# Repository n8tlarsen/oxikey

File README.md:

# Oxikey
The Rust infused, ultra-clean firmware library for building custom keyboards and other HID USB devices.

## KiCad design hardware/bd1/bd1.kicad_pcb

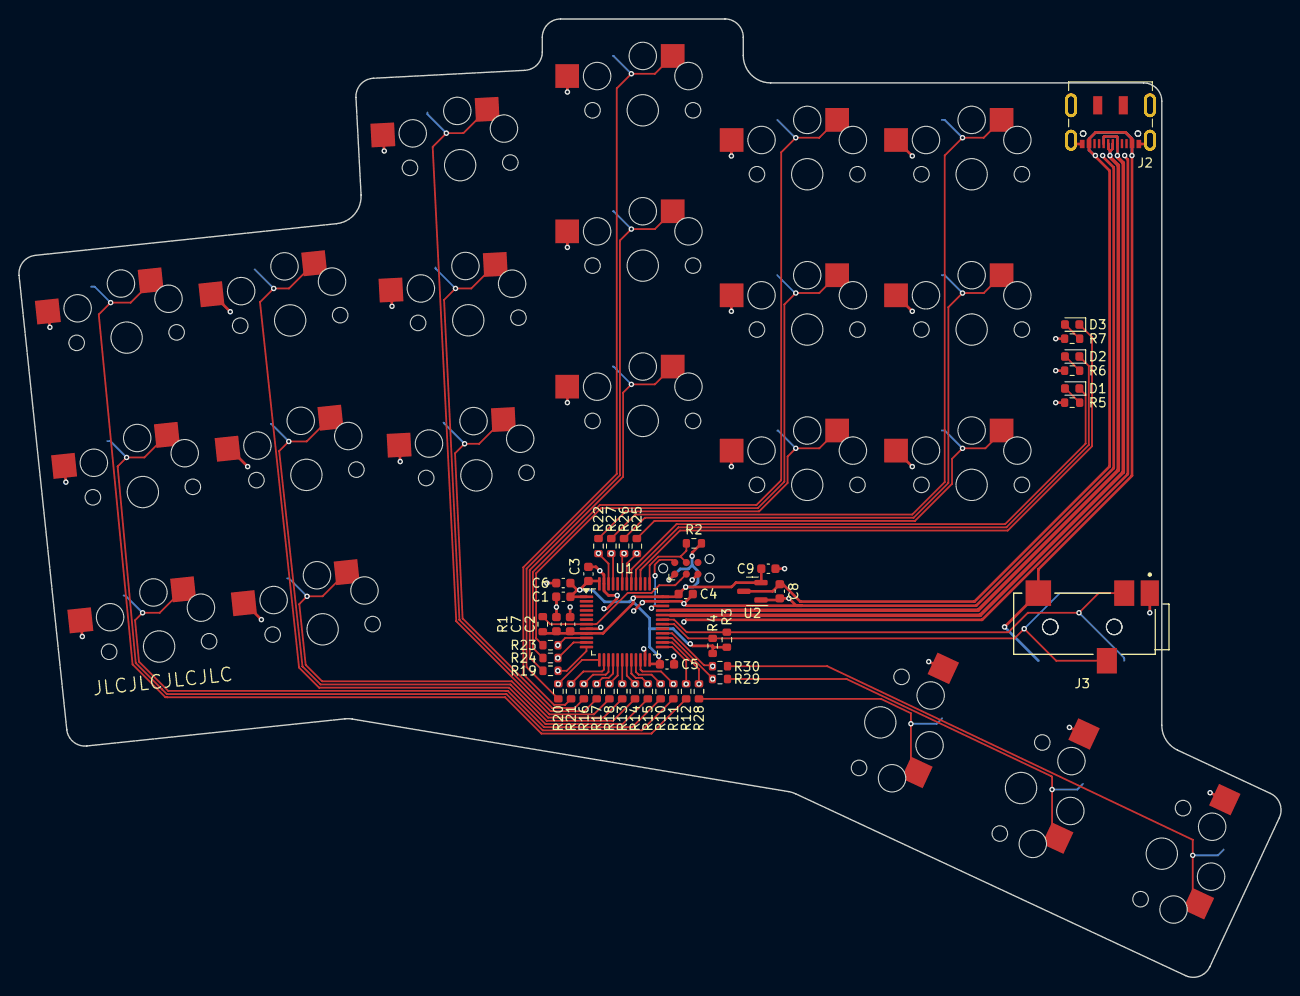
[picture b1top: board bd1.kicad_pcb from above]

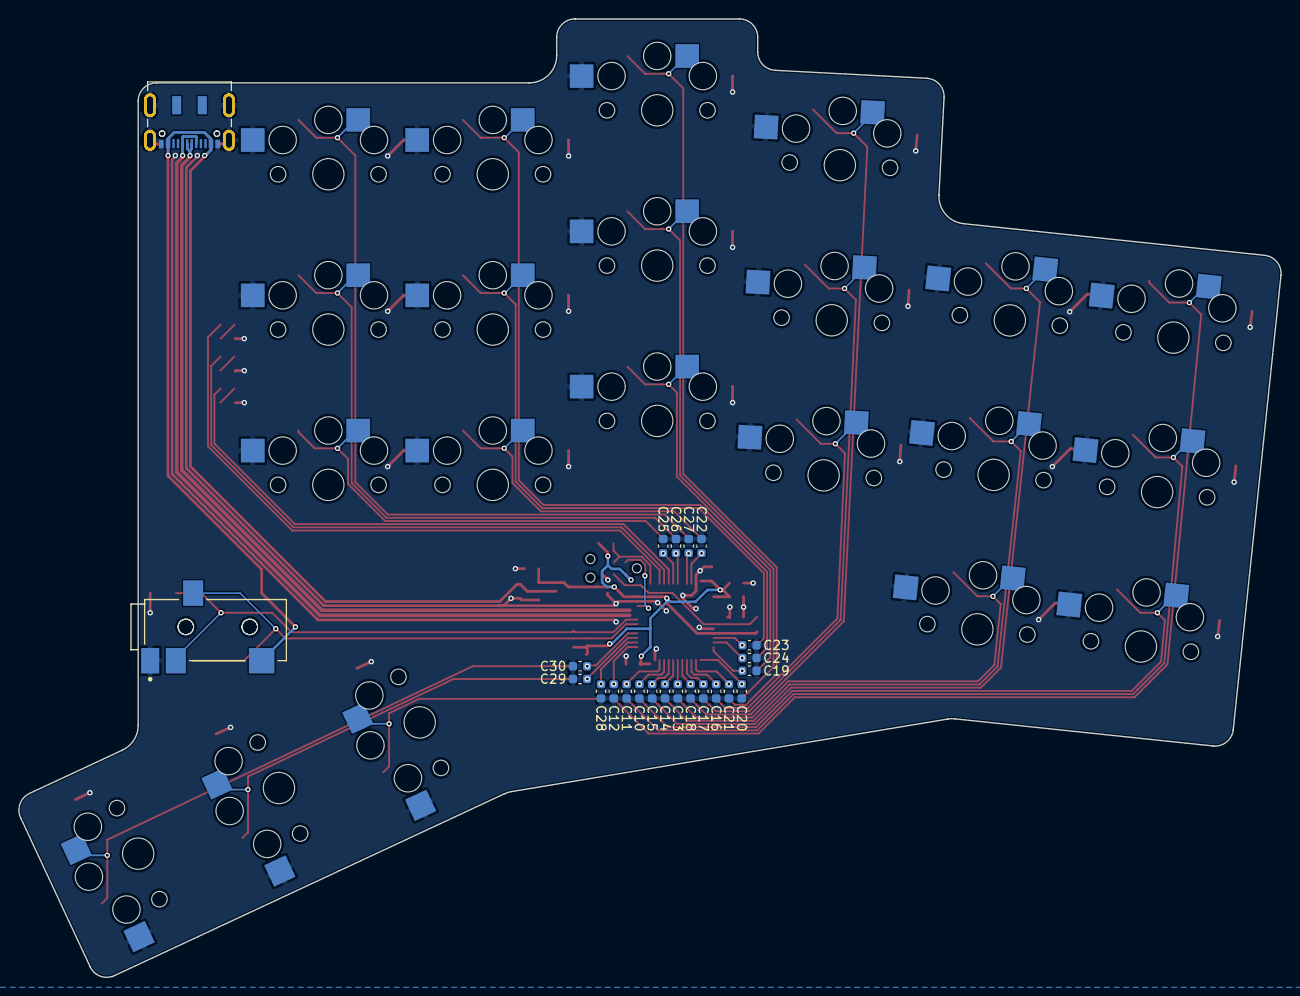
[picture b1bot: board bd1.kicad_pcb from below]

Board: 2 copper layers, 138.2 x 104.9 mm, 89 parts (23 on the bottom side), 58 nets.

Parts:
C1, C2, C3, C4, C5: 0.1uF; C_0603_1608Metric
C6: 4.7uF; C_0603_1608Metric
C7, C8, C9: 1uF; C_0603_1608Metric
C10, C11, C12, C13, C14, C15, C16, C17, C18, C19, C20, C21, C22, C23, C24, C25, C26, C27, C28, C29, C30: 4700p; C_0603_1608Metric
D1, D2, D3: LED; D_0603_1608Metric
J1: Conn_02x03_Odd_Even; Tag-Connect_TC2030-IDC-NL_2x03_P1.27mm_Vertical
J2, J20: USB_C_Receptacle_USB2.0; USB_C_Receptacle_JAE_DX07S016JA1R1500
J3, J30: SJ-43514; CUI-SJ-43514-SMT-0
R1, R3, R4: 10k; R_0603_1608Metric
R2: 1k; R_0603_1608Metric
R5, R6, R7, R10, R11, R12, R13, R14, R15, R16, R17, R18, R19, R20, R21, R22, R23, R24, R25, R26, R27, R28, R29, R30: 470; R_0603_1608Metric
S1, S2, S3, S4, S5, S6, S7, S8, S9, S10, S11, S12, S13, S14, S15, S16, S17, S18, S19, S20, S21: PG1350
U1: STM32L412CBTx; LQFP-48_7x7mm_P0.5mm
U2: AP2127N-3.3; SOT-23

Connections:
+3V3: C1.1, C2.1, C3.1, C4.1, C5.1, C6.1, C7.1, C9.1, J1.1, R1.1, R2.1, R3.1, R4.1, U1.1 (VBAT), U1.9 (VDDA), U1.24 (VDD), U1.36 (VDDUSB), U1.48 (VDD), U2.2 (VO)
+5V: C8.1, J2.A4 (VBUS), J2.A9 (VBUS), J2.B4 (VBUS), J2.B9 (VBUS), J3.2 (Tip), J20.A4 (VBUS), J20.A9 (VBUS), J20.B4 (VBUS), J20.B9 (VBUS), J30.2 (Tip), U2.3 (VI)
/LED0: D1.1 (K), U1.41 (PB5)
/LED1: D2.1 (K), U1.40 (PB4)
/LED2: D3.1 (K), U1.39 (PB3)
/PA00: C23.1, R23.2, U1.10 (PA0)
/PA01: C24.1, R24.2, U1.11 (PA1)
/PA02: C19.1, R19.2, U1.12 (PA2)
/PA03: C20.1, R20.2, U1.13 (PA3)
/PA04: C21.1, R21.2, U1.14 (PA4)
/PA05: C16.1, R16.2, U1.15 (PA5)
/PA06: C17.1, R17.2, U1.16 (PA6)
/PA07: C18.1, R18.2, U1.17 (PA7)
/PB00: C13.1, R13.2, U1.18 (PB0)
/PB01: C14.1, R14.2, U1.19 (PB1)
/PB02: C15.1, R15.2, U1.20 (PB2)
/PB06: C25.1, R25.2, U1.42 (PB6)
/PB07: C26.1, R26.2, U1.43 (PB7)
/PB08: C27.1, R27.2, U1.45 (PB8)
/PB09: C22.1, R22.2, U1.46 (PB9)
/PB10: C10.1, R10.2, U1.21 (PB10)
/PB11: C11.1, R11.2, U1.22 (PB11)
/PB12: C12.1, R12.2, U1.25 (PB12)
/PB13: C28.1, R28.2, U1.26 (PB13)
/PB14: C29.1, R29.2, U1.27 (PB14)
/PB15: C30.1, R30.2, U1.28 (PB15)
/RESETn: J1.3, R1.2, U1.7 (NRST)
/SCL: J3.3 (Ring1), J30.3 (Ring1), R4.2, U1.30 (PA9)
/SDA: J3.4 (Ring2), J30.4 (Ring2), R3.2, U1.31 (PA10)
/SWCLK: J1.4, R2.2, U1.37 (PA14)
/SWDIO: J1.2, U1.34 (PA13)
/USB_DN: J2.A7 (D-), J2.B7 (D-), J20.A7 (D-), J20.B7 (D-), U1.32 (PA11)
/USB_DP: J2.A6 (D+), J2.B6 (D+), J20.A6 (D+), J20.B6 (D+), U1.33 (PA12)
/far_thumb: R30.1, S21.1
/home_thumb: R29.1, S20.1
/index_bottom: R22.1, S13.1
/index_home: R23.1, S14.1
/index_top: R24.1, S15.1
/inner_bottom: R25.1, S16.1
/inner_home: R26.1, S17.1
/inner_top: R27.1, S18.1
/middle_bottom: R19.1, S10.1
/middle_home: R20.1, S11.1
/middle_top: R21.1, S12.1
/near_thumb: R28.1, S19.1
/outer_bottom: R10.1, S1.1
/outer_home: R11.1, S2.1
/outer_top: R12.1, S3.1
/pinky_bottom: R13.1, S4.1
/pinky_home: R14.1, S5.1
/pinky_top: R15.1, S6.1
/ring_bottom: R16.1, S7.1
/ring_home: R17.1, S8.1
/ring_top: R18.1, S9.1
GND: C1.2, C2.2, C3.2, C4.2, C5.2, C6.2, C7.2, C8.2, C9.2, C10.2, C11.2, C12.2, C13.2, C14.2, C15.2, C16.2, C17.2, C18.2, C19.2, C20.2, C21.2, C22.2, C23.2, C24.2, C25.2, C26.2, C27.2, C28.2, C29.2, C30.2, J1.5, J2.A1 (GND), J2.A12 (GND), J2.B1 (GND), J2.B12 (GND), J2.S1 (SHIELD), J3.1 (Sleeve), J20.A1 (GND), J20.A12 (GND), J20.B1 (GND), J20.B12 (GND), J20.S1 (SHIELD), J30.1 (Sleeve), R5.2, R6.2, R7.2, S1.2, S2.2, S3.2, S4.2, S5.2, S6.2, S7.2, S8.2, S9.2, S10.2, S11.2, S12.2, S13.2, S14.2, S15.2, S16.2, S17.2, S18.2, S19.2, S20.2, S21.2, U1.8 (VSSA), U1.23 (VSS), U1.35 (VSS), U1.47 (VSS), U2.1 (GND)
unnamed: D1.2 (A), R5.1
unnamed: D2.2 (A), R6.1
unnamed: D3.2 (A), R7.1

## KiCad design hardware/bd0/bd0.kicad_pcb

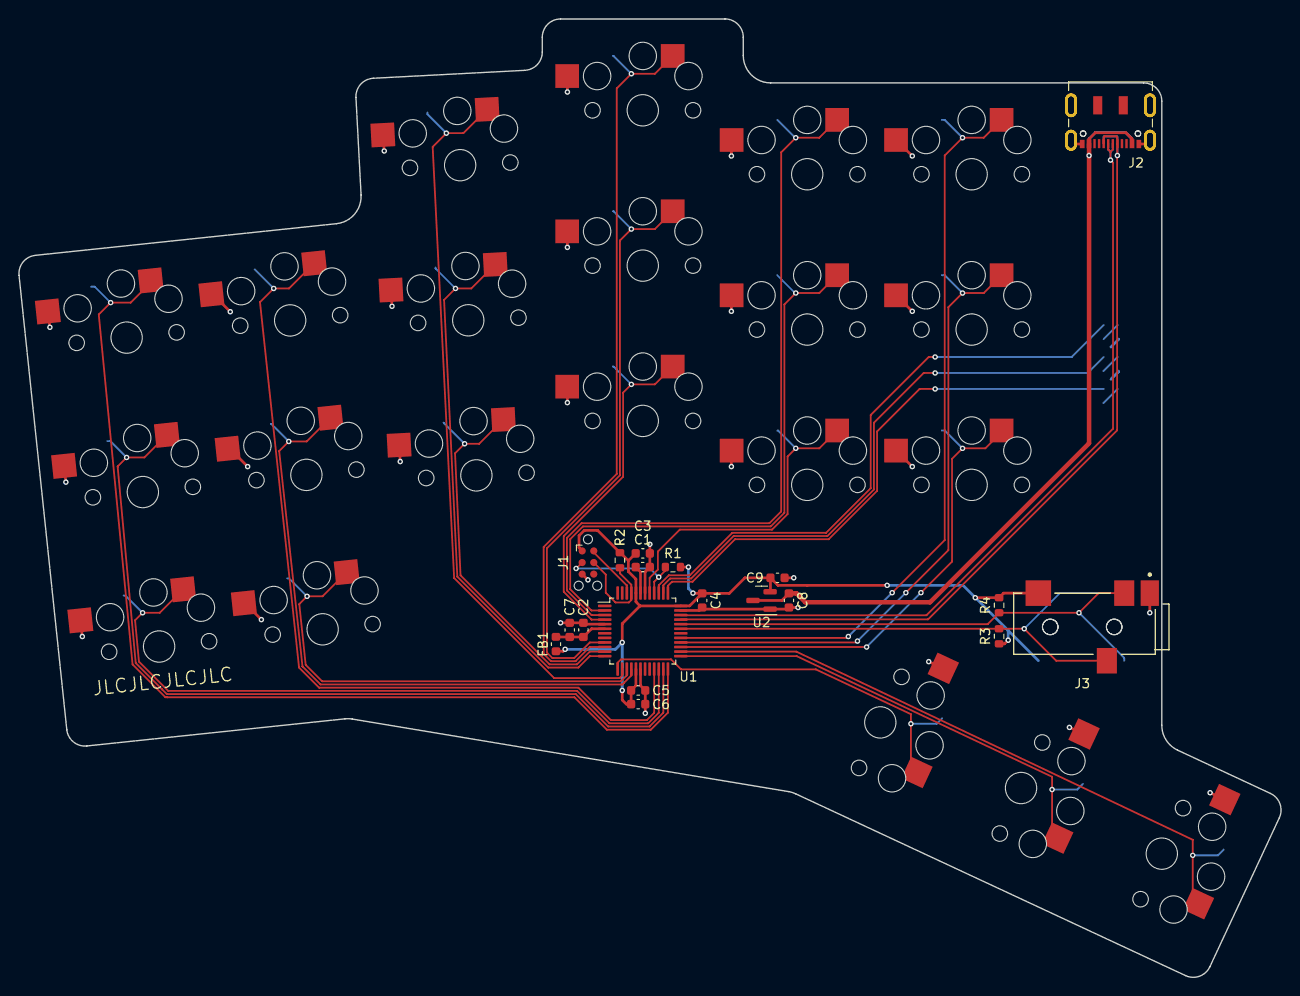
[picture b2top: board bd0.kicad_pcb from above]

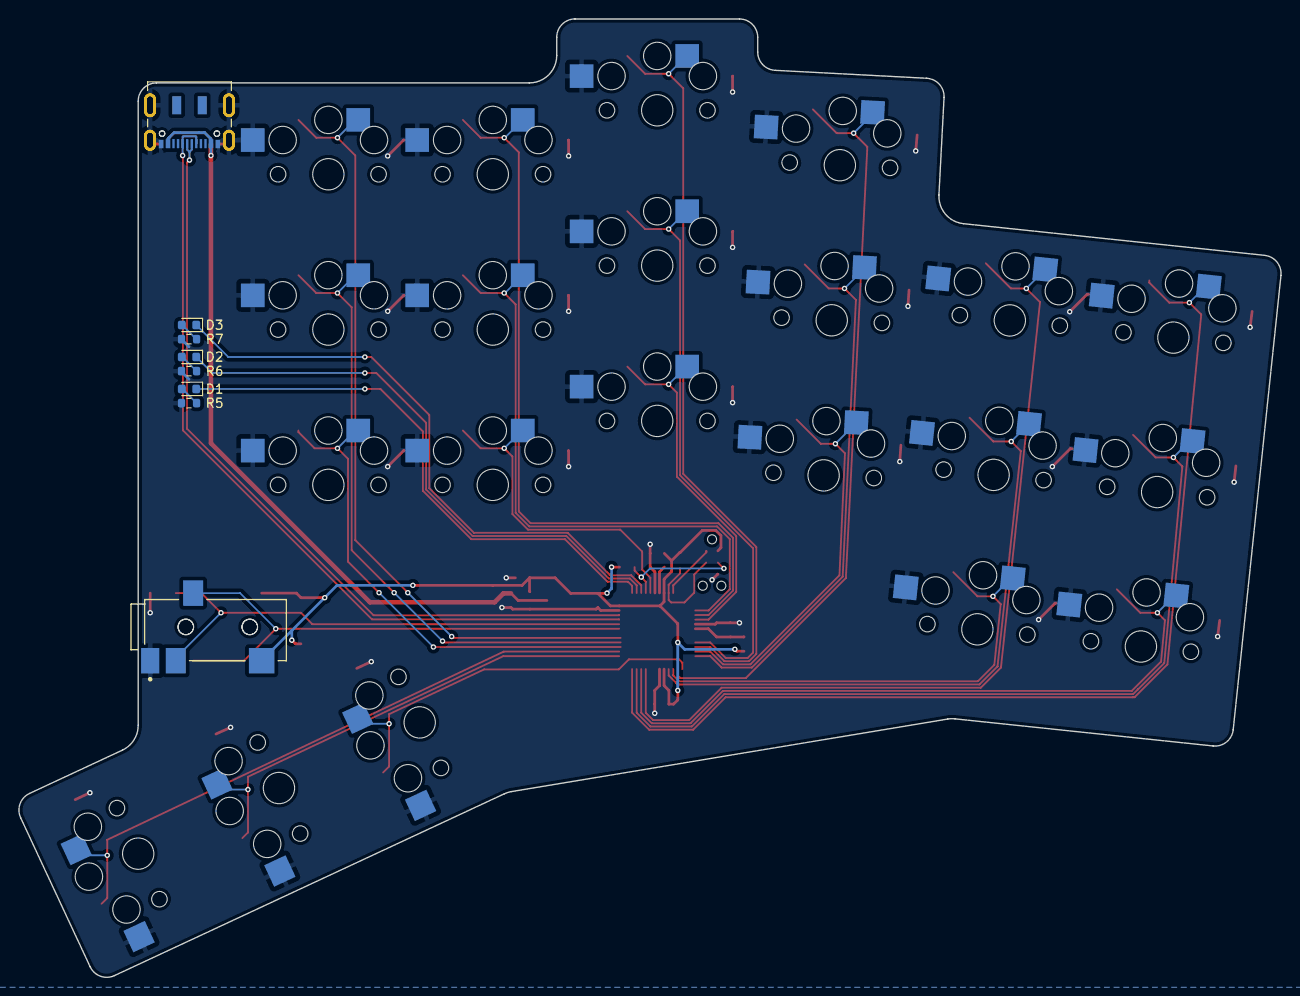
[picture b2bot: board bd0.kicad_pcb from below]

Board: 2 copper layers, 138.2 x 104.9 mm, 48 parts (8 on the bottom side), 39 nets.

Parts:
C1, C8, C9: 1uF; C_0603_1608Metric
C2, C3, C4, C5: 0.1uF; C_0603_1608Metric
C6, C7: 10uF; C_0603_1608Metric
D1, D2, D3: LED; D_0603_1608Metric
FB1: FerriteBead; L_0603_1608Metric
J1: Conn_02x03_Odd_Even; Tag-Connect_TC2030-IDC-NL_2x03_P1.27mm_Vertical
J2, J20: USB_C_Receptacle_USB2.0; USB_C_Receptacle_JAE_DX07S016JA1R1500
J3, J30: SJ-43514; CUI-SJ-43514-SMT-0
R1, R3, R4: 10k; R_0603_1608Metric
R2: 1k; R_0603_1608Metric
R5, R6, R7: 470; R_0603_1608Metric
S1, S2, S3, S4, S5, S6, S7, S8, S9, S10, S11, S12, S13, S14, S15, S16, S17, S18, S19, S20, S21: PG1350
U1: ATSAMD21G15B-A; TQFP-48_7x7mm_P0.5mm
U2: AP2127N-3.3; SOT-23

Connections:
+1V2: C1.1, U1.43 (VDDCORE)
+3V3: C3.1, C4.1, C5.1, C6.1, C9.1, FB1.1, J1.1, J3.2 (Tip), J30.2 (Tip), R1.1, R2.1, R3.1, R4.1, U1.17 (VDDIO), U1.36 (VDDIO), U1.44 (VDDIN), U2.2 (VO)
+5V: C8.1, J2.A4 (VBUS), J2.A9 (VBUS), J2.B4 (VBUS), J2.B9 (VBUS), J20.A4 (VBUS), J20.A9 (VBUS), J20.B4 (VBUS), J20.B9 (VBUS), U2.3 (VI)
/3V3A: C2.1, C7.1, FB1.2, U1.6 (VDDANA)
/LED0: D1.1 (K), U1.37 (PB22)
/LED1: D2.1 (K), U1.38 (PB23)
/LED2: D3.1 (K), U1.39 (PA27)
/RESETn: J1.3, R1.2, U1.40 (~RESET)
/SCL: J3.4 (Ring2), J30.4 (Ring2), R4.2, U1.32 (PA23)
/SDA: J3.3 (Ring1), J30.3 (Ring1), R3.2, U1.31 (PA22)
/SWCLK: J1.4, R2.2, U1.45 (PA30)
/SWDIO: J1.2, U1.46 (PA31)
/USB_DN: J2.A7 (D-), J2.B7 (D-), J20.A7 (D-), J20.B7 (D-), U1.33 (PA24)
/USB_DP: J2.A6 (D+), J2.B6 (D+), J20.A6 (D+), J20.B6 (D+), U1.34 (PA25)
/far_thumb: S21.1, U1.26 (PA17)
/home_thumb: S20.1, U1.25 (PA16)
/index_bottom: S13.1, U1.41 (PA28)
/index_home: S14.1, U1.2 (PA01)
/index_top: S15.1, U1.3 (PA02)
/inner_bottom: S16.1, U1.27 (PA18)
/inner_home: S17.1, U1.28 (PA19)
/inner_top: S18.1, U1.29 (PA20)
/middle_bottom: S10.1, U1.4 (PA03)
/middle_home: S11.1, U1.9 (PA04)
/middle_top: S12.1, U1.10 (PA05)
/near_thumb: S19.1, U1.13 (PA08)
/outer_bottom: S1.1, U1.22 (PA13)
/outer_home: S2.1, U1.23 (PA14)
/outer_top: S3.1, U1.24 (PA15)
/pinky_bottom: S4.1, U1.15 (PA10)
/pinky_home: S5.1, U1.16 (PA11)
/pinky_top: S6.1, U1.21 (PA12)
/ring_bottom: S7.1, U1.11 (PA06)
/ring_home: S8.1, U1.12 (PA07)
/ring_top: S9.1, U1.14 (PA09)
GND: C1.2, C2.2, C3.2, C4.2, C5.2, C6.2, C7.2, C8.2, C9.2, J1.5, J2.A1 (GND), J2.A12 (GND), J2.B1 (GND), J2.B12 (GND), J2.S1 (SHIELD), J3.1 (Sleeve), J20.A1 (GND), J20.A12 (GND), J20.B1 (GND), J20.B12 (GND), J20.S1 (SHIELD), J30.1 (Sleeve), R5.2, R6.2, R7.2, S1.2, S2.2, S3.2, S4.2, S5.2, S6.2, S7.2, S8.2, S9.2, S10.2, S11.2, S12.2, S13.2, S14.2, S15.2, S16.2, S17.2, S18.2, S19.2, S20.2, S21.2, U1.5 (GNDANA), U1.18 (GND), U1.35 (GND), U1.42 (GND), U2.1 (GND)
unnamed: D1.2 (A), R5.1
unnamed: D2.2 (A), R6.1
unnamed: D3.2 (A), R7.1

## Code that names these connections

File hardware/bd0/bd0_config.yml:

points:
  key:
    padding: cy
    footprints:
      keychoc:
        type: choc
        nets:
          from: =keynet
          to: GND
        params:
          hotswap: true
          reverse: true
          keycaps: true
  zones:
    matrix:
      anchor:
      rows:
        bottom:
          bind: [1,2,1,2]
        home:
          bind: [1,2,1,2]
        top:
          bind: [1,2,1,2]
      columns:
        outer:
          spread: cx
          rotate: 6
          row_overrides:
            bottom:
              keynet: /outer_bottom
            home:
              keynet: /outer_home
            top:
              keynet: /outer_top
        pinky:
          spread: cx
          row_overrides:
            bottom:
              keynet: /pinky_bottom
            home:
              keynet: /pinky_home
            top:
              keynet: /pinky_top
        ring:
          spread: cx+0.5
          rotate: -3
          stagger: 15
          row_overrides:
            bottom:
              keynet: /ring_bottom
            home:
              keynet: /ring_home
            top:
              keynet: /ring_top
        middle:
          spread: cx+0.5
          rotate: -3
          stagger: 5
          row_overrides:
            bottom:
              keynet: /middle_bottom
            home:
              keynet: /middle_home
            top:
              keynet: /middle_top
        index:
          spread: cx
          stagger: -7
          row_overrides:
            bottom:
              keynet: /index_bottom
            home:
              keynet: /index_home
            top:
              keynet: /index_top
        inner:
          spread: cx
          row_overrides:
            bottom:
              keynet: /inner_bottom
            home:
              keynet: /inner_home
            top:
              keynet: /inner_top
    thumbfan:
      anchor:
        ref: matrix_inner_bottom
        shift: [-10, -26]
        rotate: -25
      rows:
        thumb:
          bind: [1,2,1,2]
      columns:
        near:
          key:
            rotate: -90
          row_overrides:
            thumb:
              keynet: /near_thumb
        home:
          spread: cy
          key:
            rotate: -90
          row_overrides:
            thumb:
              keynet: /home_thumb
        far:
          spread: cy
          key:
            rotate: -90
          row_overrides:
            thumb:
              keynet: /far_thumb
outlines:
  exports:
    raw:
      - type: keys
        side: left
        size: [cx, cx]
      - operation: add
        type: polygon
        points: 
          - ref: matrix_pinky_bottom
            shift: [0,-cy/2-1]
          - ref: thumbfan_far_thumb
            # shift: [0   , cy/2]
          - ref: matrix_inner_top
            shift: [20.81446479999999, 1.5+cy/2]
          - ref: matrix_index_top
            shift: [0, 1.5+cy/2]
          # - ref: matrix_inner_bottom
          #   shift: [cx/2,cy/2+1]
          - ref: matrix_index_bottom
          - ref: matrix_pinky_home
    cutout:
      - type: outline
        name: raw
        fillet: 3
      - operation: add
        type: outline
        name: raw
        fillet: 2
    keycap_outlines:
      - type: keys
        side: left
        size: [cx-0.5, cy-0.5]
        bound: false

pcbs:
  bd0:
    outlines:
      bd:
        outline: cutout

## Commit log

2022-08-07 Add base files from rust-embedded/cortex-m-quickstart
2022-08-13 Add basic RTIC framework
2022-08-14 Add module for device initialization
2022-08-19 Condense setup to a single function
2022-08-28 Fix crashing issue when starting DFLL
2022-09-01 Use semihosting only in debug configuration
2022-09-05 Use forked HAL for clock setup
2022-09-24 Clock at 48MHz with 1Hz blink
2022-09-25 Add usbd-hid
2022-11-29 USB HID device connected to PC
2022-11-30 Migrate setup from dev board to real keyboard
2022-11-30 Restructure to library with examples
2022-11-30 Rename 'oxy-' to 'oxi-' to reflect 'oxide'
2022-11-30 Add hardware sources for bd0
2022-11-30 Update .gitignore for KiCad
2022-12-02 Add Debounce struct
2022-12-03 Read pin input register
2022-12-06 Add simple keyboard report generation
2022-12-16 USB now reports keys to host
2023-01-15 Add defmt and update USB pid
2023-01-15 Use git deps instead of paths
2023-05-21 Update to RTIC v2
2023-05-21 Setup defmt over rtt
2024-06-16 Add STM32 and RC filters
2024-06-16 USB routing
2024-06-17 Add splayed thumb fan
2024-06-17 Fix footprint and net generation
2024-11-30 Add tmp* directories to gitignore
2024-11-30 Solved routing
2024-11-30 Shift MCU so programmer has room
2025-01-01 Finish silkscreen
